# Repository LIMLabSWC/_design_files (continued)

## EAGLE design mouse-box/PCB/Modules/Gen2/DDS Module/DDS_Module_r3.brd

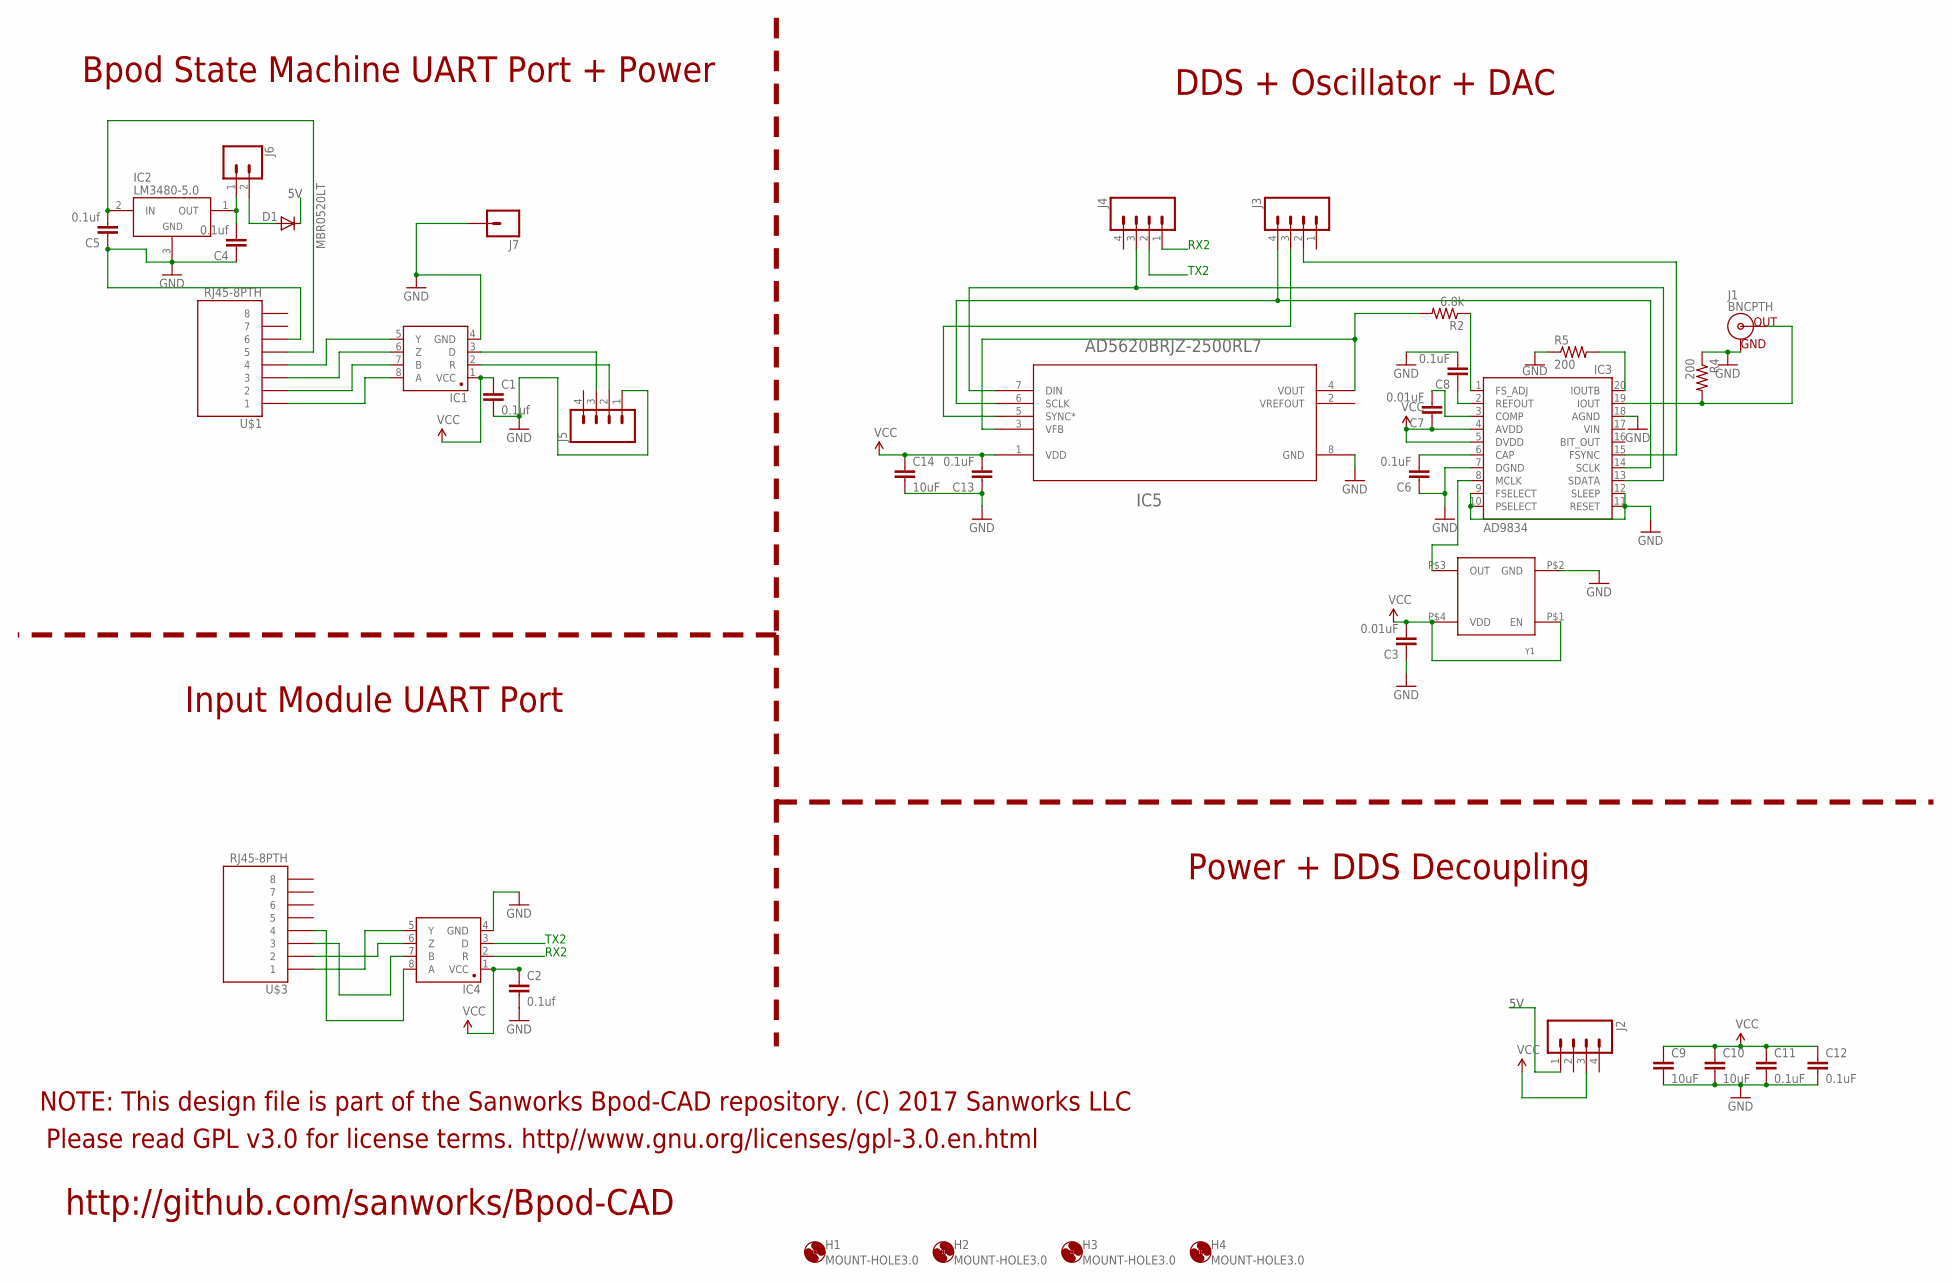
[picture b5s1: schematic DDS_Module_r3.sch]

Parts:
C1, C2, C4, C5: 0.1uf; 1206@1
C3, C7: 0.01uF; 0805
C6, C8, C11, C12, C13: 0.1uF; 0805
C9, C10, C14: 10uF; 0805
D1: MBR0520LT; SOD123
H1, H2, H3, H4: MOUNT-HOLE3.0; 3,0
IC1, IC4: SN65HVD31DR; SO08
IC2: LM3480-5.0; SOT-23-3
IC3: AD9834; TSSOP20
IC5: AD5620BRJZ-2500RL7; RJ_8
J1: BNCPTH; BNC
J2, J3, J4, J5: M04PTH; 1X04
J6: CONN_02; 1X02
J7: M01PTH; 1X01
R2: 6.8k; R0805
R4, R5: 200; R0805
U$1, U$3: RJ45-8PTH; RJ45-8
Y1: ASE10MHZ

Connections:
5V: D1.C, J2.1
GND: C1.2, C2.2, C3.1, C4.1, C5.1, C6.1, C8.2, C9.2, C10.2, C11.2, C12.2, C13.1, C14.2, IC1.4 (GND), IC2.3 (GND), IC3.7 (DGND), IC3.9 (FSELECT), IC3.10 (PSELECT), IC3.11 (RESET), IC3.12 (SLEEP), IC3.18 (AGND), IC4.4 (GND), IC5.8 (GND), J1.GND, J5.1, J7.1, R4.1, R5.1, U$1.6, Y1.P$2 (GND)
unnamed: IC3.13 (SDATA), IC5.7 (DIN), J4.3
unnamed: IC3.14 (SCLK), IC5.6 (SCLK), J3.4
unnamed: IC5.5 (SYNC*), J3.3
unnamed: IC3.20 (IOUTB), R5.2
unnamed: IC3.15 (FSYNC), J3.2
unnamed: IC3.1 (FS_ADJ), R2.1
unnamed: IC1.8 (A), U$1.1
unnamed: IC1.7 (B), U$1.2
unnamed: IC1.6 (Z), U$1.3
unnamed: IC1.5 (Y), U$1.4
unnamed: IC5.3 (VFB), IC5.4 (VOUT), R2.2
unnamed: IC3.8 (MCLK), Y1.P$3 (OUT)
unnamed: IC3.19 (IOUT), J1.S (OUT), R4.2
unnamed: C4.2, IC2.1 (OUT), J6.1
unnamed: C6.2, IC3.6 (CAP)
unnamed: C7.2, IC3.3 (COMP)
unnamed: C8.1, IC3.2 (REFOUT)
unnamed: D1.A, J6.2
unnamed: IC4.5 (Y), U$3.1
unnamed: IC4.6 (Z), U$3.2
unnamed: IC4.7 (B), U$3.3
unnamed: C5.2, IC2.2 (IN), U$1.5
unnamed: IC4.8 (A), U$3.4
RX1: IC1.2 (R), J5.2
RX2: IC4.2 (R), J4.1
TX1: IC1.3 (D), J5.3
TX2: IC4.3 (D), J4.2
VCC: C1.1, C2.1, C3.2, C7.1, C9.1, C10.1, C11.1, C12.1, C13.2, C14.1, IC1.1 (VCC), IC3.4 (AVDD), IC3.5 (DVDD), IC4.1 (VCC), IC5.1 (VDD), J2.3, Y1.P$1 (EN), Y1.P$4 (VDD)

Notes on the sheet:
RX2
TX2
Bpod State Machine UART Port + Power
Input Module UART Port
DDS + Oscillator + DAC
Power + DDS Decoupling
Please read GPL v3.0 for license terms. http//www.gnu.org/licenses/gpl-3.0.en.html
NOTE: This design file is part of the Sanworks Bpod-CAD repository. (C) 2017 Sanworks LLC
http://github.com/sanworks/Bpod-CAD

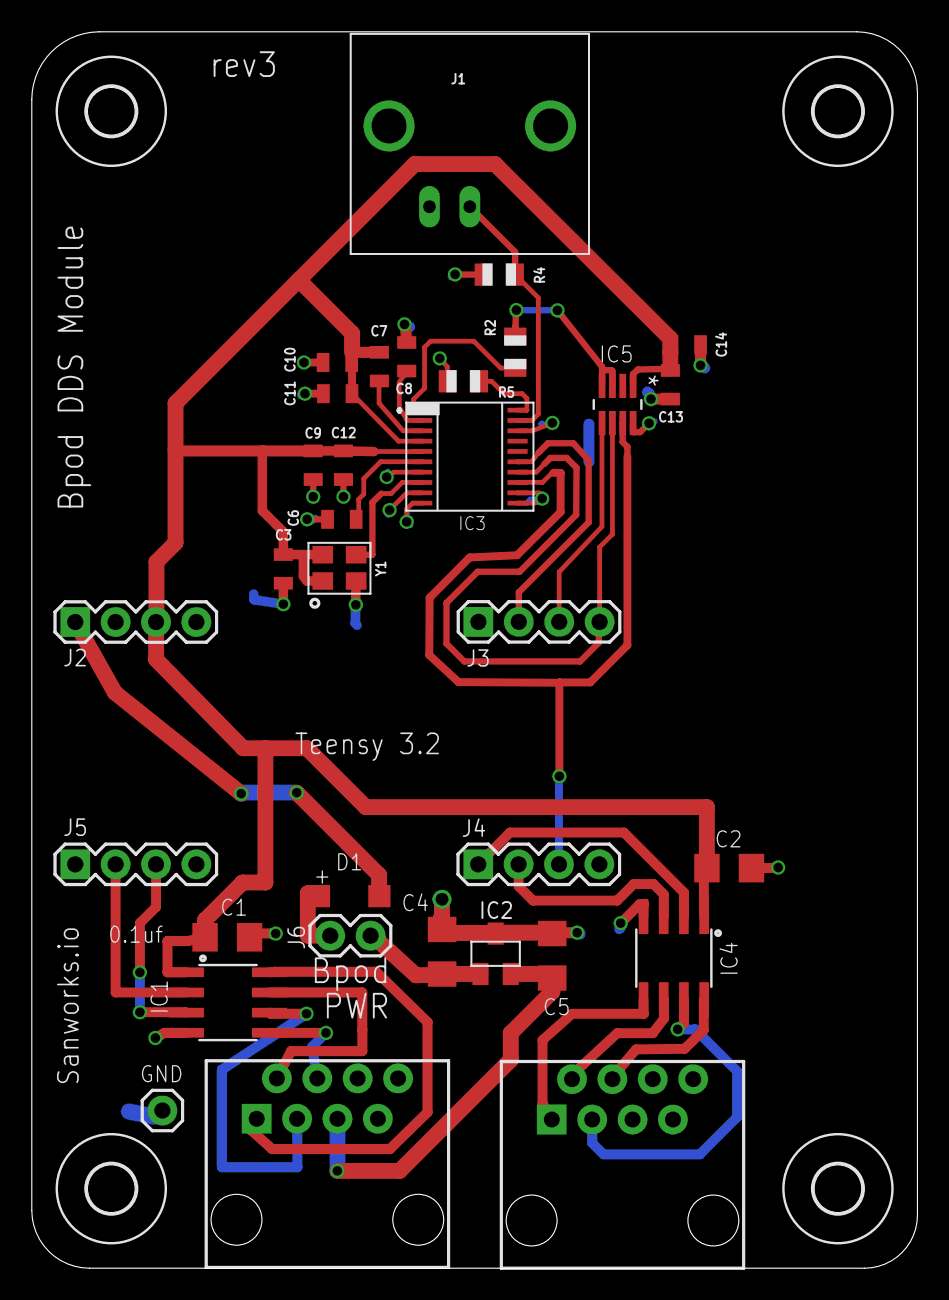
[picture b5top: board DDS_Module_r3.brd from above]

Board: 2 copper layers, 55.7 x 77.8 mm, 37 parts (0 on the bottom side), 30 nets.

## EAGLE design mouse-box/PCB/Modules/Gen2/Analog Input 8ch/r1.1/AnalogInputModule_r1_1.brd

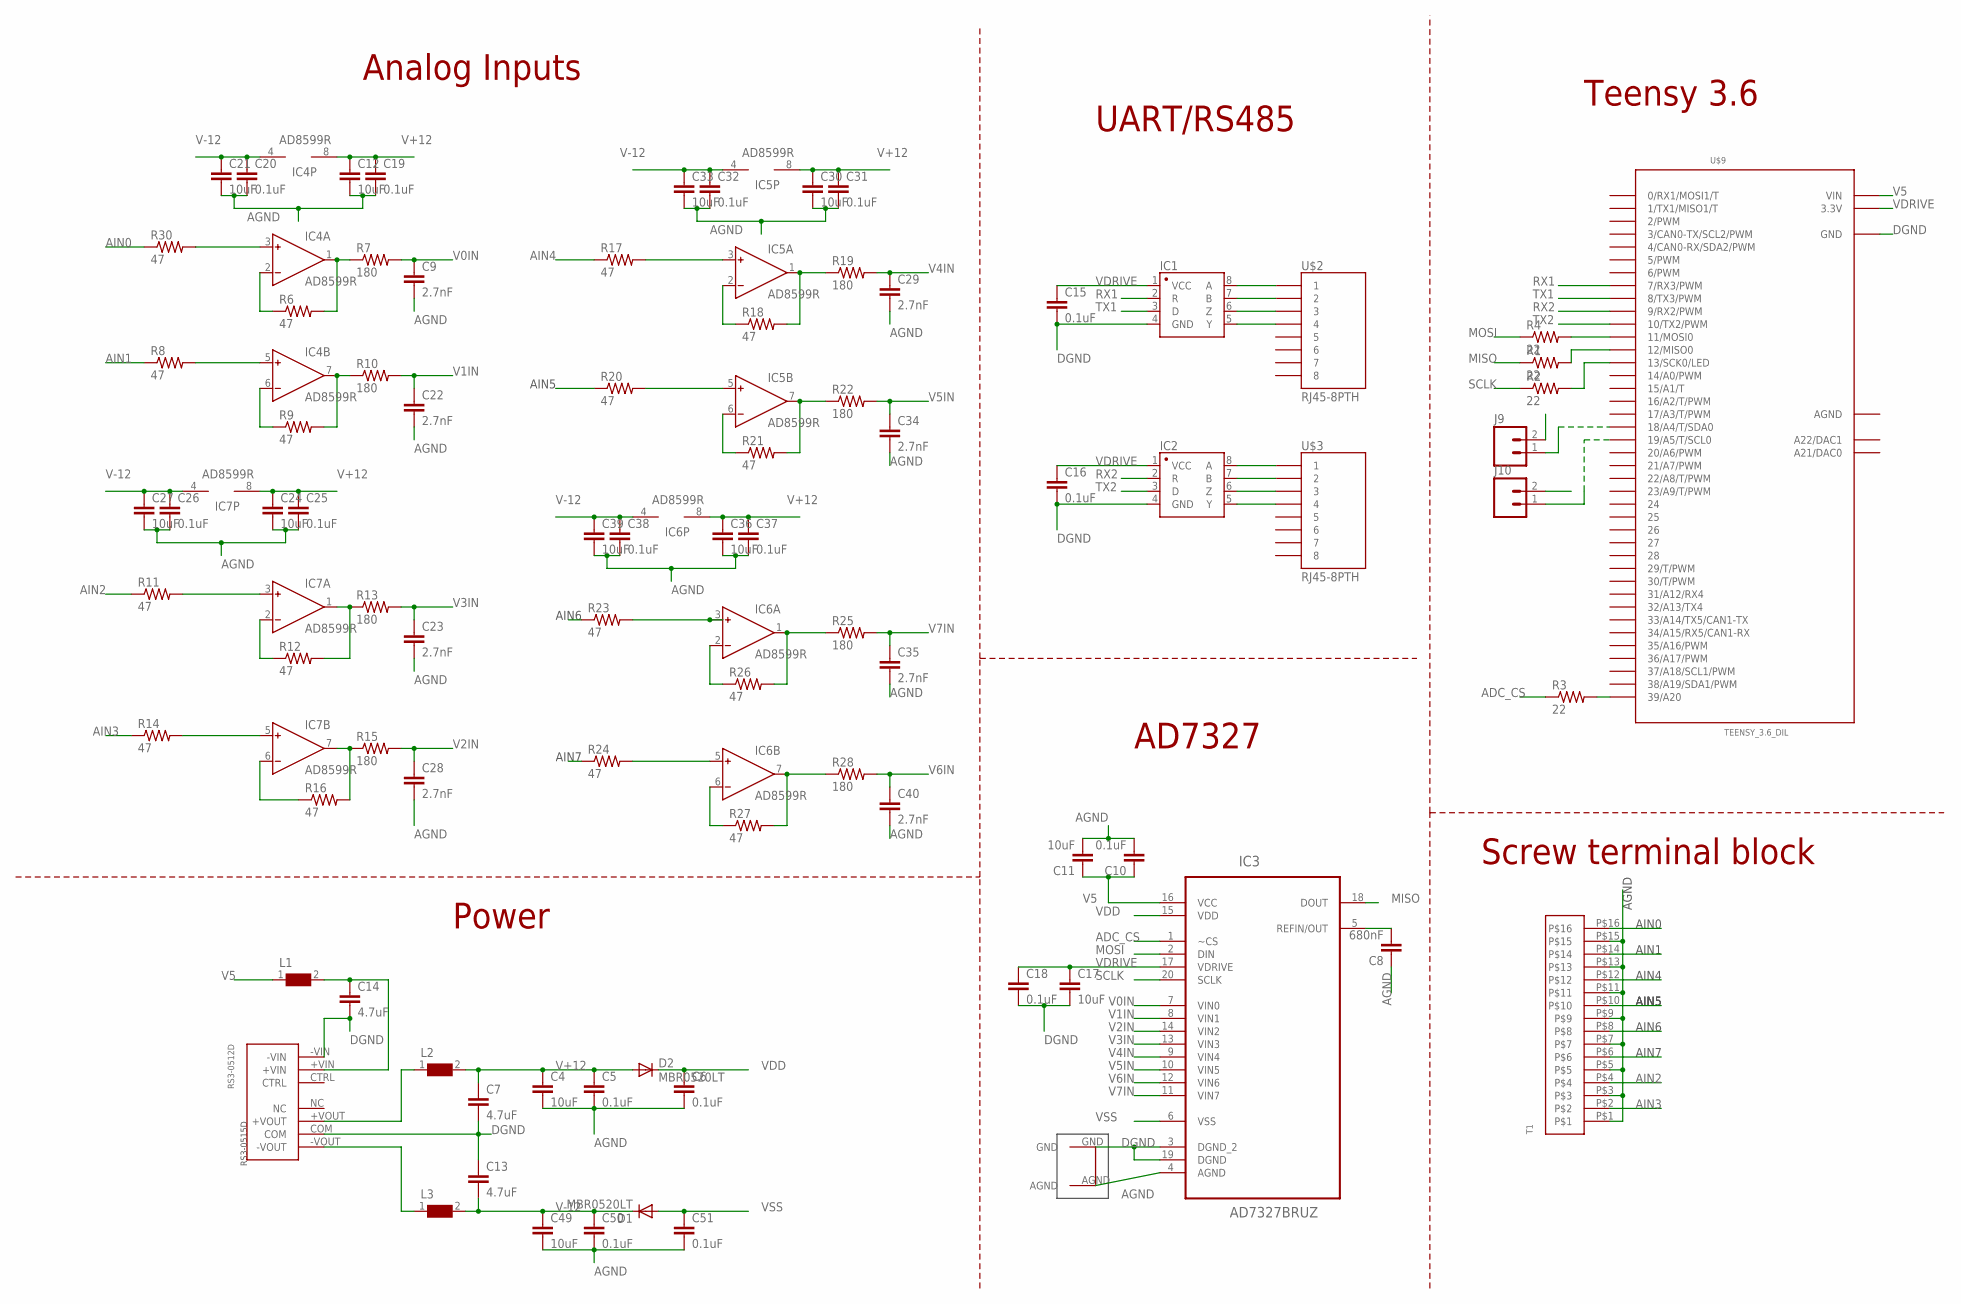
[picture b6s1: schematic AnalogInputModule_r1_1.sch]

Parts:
C4, C11, C12, C17, C21, C24, C27, C30, C33, C36, C39, C49: 10uF; 0805
C5, C6, C10, C15, C16, C18, C19, C20, C25, C26, C31, C32, C37, C38, C50, C51: 0.1uF; 0805
C7, C13, C14: 4.7uF; 1206
C8: 680nF; 0805
C9, C22, C23, C28, C29, C34, C35, C40: 2.7nF; 0805
D1, D2: MBR0520LT; SOD123
IC1, IC2: SN65HVD31DR; SO08
IC3: AD7327BRUZ; SOP65P640X120-20N
IC4, IC5, IC6, IC7: AD8599R; SO8
J9, J10: M023.5MM; SCREWTERMINAL-3.5MM-2
L1, L2, L3: WE-CBF-742792118_1206; 1206
R1, R2, R3, R4: 22; R0805
R6, R8, R9, R11, R12, R14, R16, R17, R18, R20, R21, R23, R24, R26, R27, R30: 47; R0805
R7, R10, R13, R15, R19, R22, R25, R28: 180; R0805
RS3-0512D: RS3-0515D
T1: 16POS_SCREWTERMINAL
U$2, U$3: RJ45-8PTH; RJ45-8
U$4: GNDPLANESHRT
U$9: TEENSY_3.6_DIL

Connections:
+VOUT: L2.1, RS3-0512D.+VOUT
-VOUT: L3.1, RS3-0512D.-VOUT
ADC_CS: IC3.1 (~CS), R3.1
AGND: C4.2, C5.2, C6.2, C8.1, C9.2, C10.2, C11.2, C12.2, C19.2, C20.2, C21.2, C22.2, C23.2, C24.2, C25.2, C26.2, C27.2, C28.2, C29.2, C30.2, C31.2, C32.2, C33.2, C34.2, C35.2, C36.2, C37.2, C38.2, C39.2, C40.2, C49.2, C50.2, C51.2, IC3.4 (AGND), T1.P$1, T1.P$3, T1.P$5, T1.P$7, T1.P$9, T1.P$11, T1.P$13, T1.P$15, U$4.AGND, U$9.AGND
AIN0: R30.1, T1.P$16
AIN1: R8.1, T1.P$14
AIN2: R11.1, T1.P$4
AIN3: R14.1, T1.P$2
AIN4: R17.1, T1.P$12
AIN5: R20.1, T1.P$10
AIN6: R23.1, T1.P$8
AIN7: R24.1, T1.P$6
DGND: C7.2, C13.1, C14.2, C15.2, C16.2, C17.2, C18.2, IC1.4 (GND), IC2.4 (GND), IC3.3 (DGND_2), IC3.19 (DGND), J9.2, J10.2, RS3-0512D.-VIN, RS3-0512D.COM, U$4.GND, U$9.GND, U$9.GND1 (GND)
MISO: IC3.18 (DOUT), R1.1
MOSI: IC3.2 (DIN), R4.1
unnamed: IC1.6 (Z), U$2.3
unnamed: IC1.8 (A), U$2.1
unnamed: IC1.5 (Y), U$2.4
unnamed: IC1.7 (B), U$2.2
unnamed: IC2.6 (Z), U$3.3
unnamed: IC2.5 (Y), U$3.4
unnamed: IC2.8 (A), U$3.1
unnamed: IC2.7 (B), U$3.2
unnamed: R4.2, U$9.11 (11/MOSI0)
unnamed: R1.2, U$9.12 (12/MISO0)
unnamed: C14.1, L1.2, RS3-0512D.+VIN
unnamed: R3.2, U$9.39/A20
unnamed: IC4.3 (IN+), R30.2
unnamed: R2.2, U$9.13 (13/SCK0/LED)
unnamed: IC4.2 (IN-), R6.1
unnamed: IC4.1 (OUT), R6.2, R7.1
unnamed: J9.1, U$9.18/A4 (18/A4/T/SDA0)
unnamed: J10.1, U$9.19/A5 (19/A5/T/SCL0)
unnamed: IC4.5 (IN+), R8.2
unnamed: IC4.6 (IN-), R9.1
unnamed: IC4.7 (OUT), R9.2, R10.1
unnamed: IC7.3 (IN+), R11.2
unnamed: IC7.2 (IN-), R12.1
unnamed: IC7.1 (OUT), R12.2, R13.1
unnamed: IC7.5 (IN+), R14.2
unnamed: IC7.6 (IN-), R16.1
unnamed: IC7.7 (OUT), R15.1, R16.2
unnamed: IC5.3 (IN+), R17.2
unnamed: IC5.2 (IN-), R18.1
unnamed: IC5.1 (OUT), R18.2, R19.1
unnamed: IC5.5 (IN+), R20.2
unnamed: IC5.6 (IN-), R21.1
unnamed: IC5.7 (OUT), R21.2, R22.1
unnamed: IC6.3 (IN+), R23.2
unnamed: IC6.2 (IN-), R26.1
unnamed: IC6.1 (OUT), R25.1, R26.2
unnamed: IC6.5 (IN+), R24.2
unnamed: IC6.6 (IN-), R27.1
unnamed: IC6.7 (OUT), R27.2, R28.1
REF: C8.2, IC3.5 (REFIN/OUT)
RX1: IC1.2 (R), U$9.7 (7/RX3/PWM)
RX2: IC2.2 (R), U$9.9 (9/RX2/PWM)
SCLK: IC3.20 (SCLK), R2.1
TX1: IC1.3 (D), U$9.8 (8/TX3/PWM)
TX2: IC2.3 (D), U$9.10 (10/TX2/PWM)
V0IN: C9.1, IC3.7 (VIN0), R7.2
V1IN: C22.1, IC3.8 (VIN1), R10.2
V2IN: C28.1, IC3.14 (VIN2), R15.2
V3IN: C23.1, IC3.13 (VIN3), R13.2
V4IN: C29.1, IC3.9 (VIN4), R19.2
V5: C10.1, C11.1, IC3.16 (VCC), L1.1, U$9.VIN
V5IN: C34.1, IC3.10 (VIN5), R22.2
V6IN: C40.1, IC3.12 (VIN6), R28.2
V7IN: C35.1, IC3.11 (VIN7), R25.2
V+12: C4.1, C5.1, C7.1, C12.1, C19.1, C24.1, C25.1, C30.1, C31.1, C36.1, C37.1, D2.A, IC4.8 (V+), IC5.8 (V+), IC6.8 (V+), IC7.8 (V+), L2.2
V-12: C13.2, C20.1, C21.1, C26.1, C27.1, C32.1, C33.1, C38.1, C39.1, C49.1, C50.1, D1.C, IC4.4 (V-), IC5.4 (V-), IC6.4 (V-), IC7.4 (V-), L3.2
VDD: C6.1, D2.C, IC3.15 (VDD)
VDRIVE: C15.1, C16.1, C17.1, C18.1, IC1.1 (VCC), IC2.1 (VCC), IC3.17 (VDRIVE), U$9.3.3V, U$9.3.3V3 (3.3V)
VSS: C51.1, D1.A, IC3.6 (VSS)

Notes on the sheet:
Teensy 3.6
UART/RS485
AD7327
Analog Inputs
Power
Screw terminal block
AIN7
AIN6
AIN5
AIN4
AIN1
AIN0
AGND

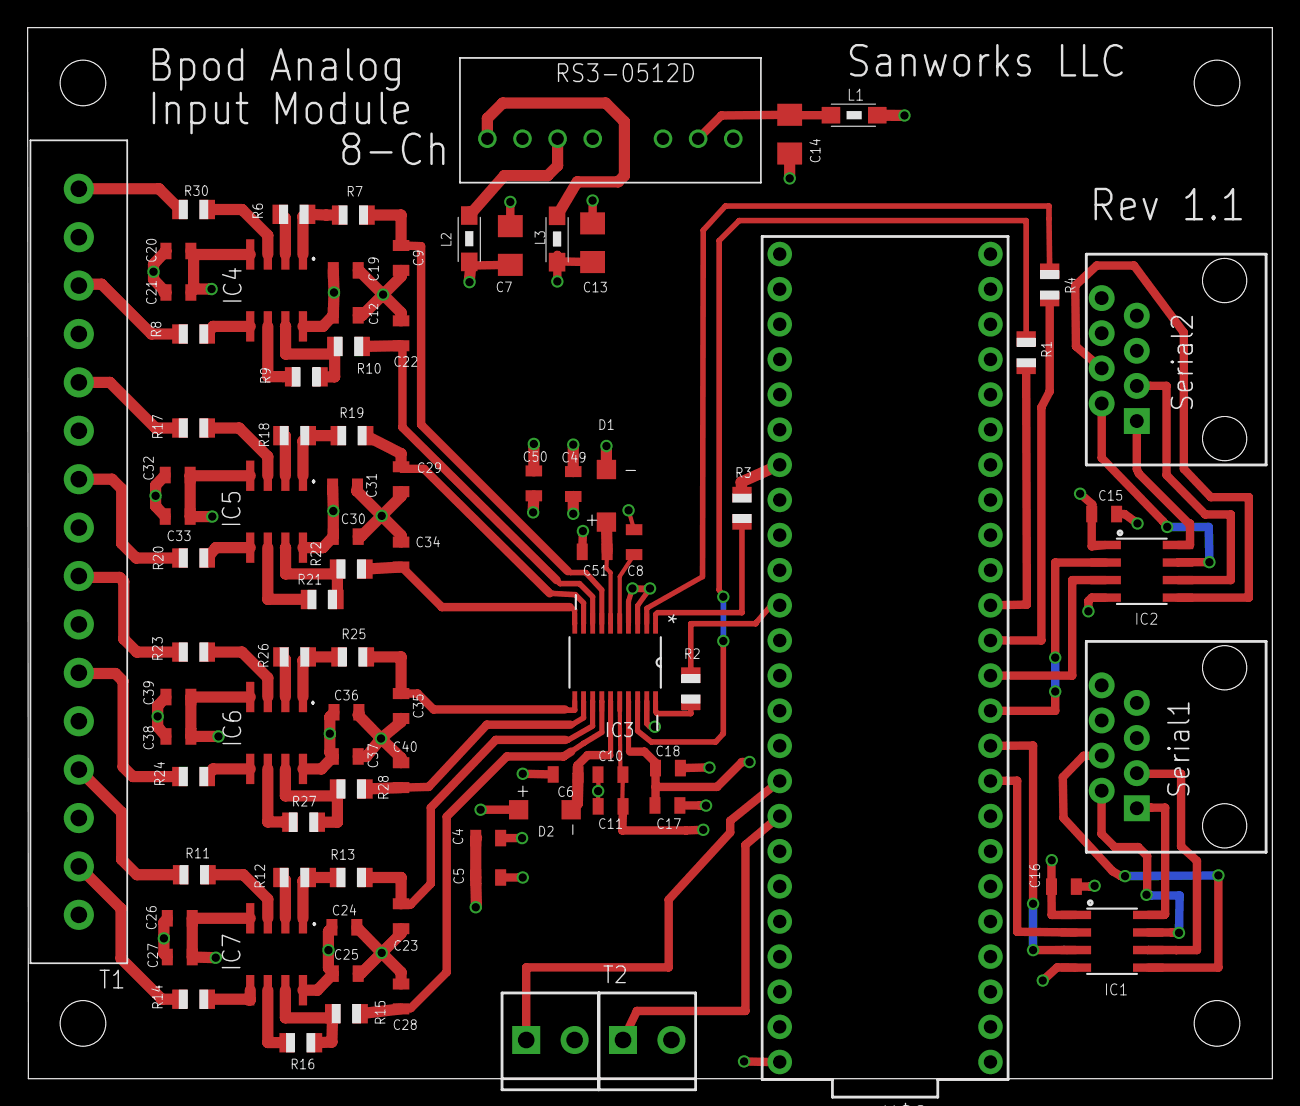
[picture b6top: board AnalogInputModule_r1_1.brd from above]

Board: 4 copper layers, 90.0 x 76.0 mm, 92 parts (0 on the bottom side), 74 nets.

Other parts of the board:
U$5, U$6, U$7, U$8: STAND-OFF

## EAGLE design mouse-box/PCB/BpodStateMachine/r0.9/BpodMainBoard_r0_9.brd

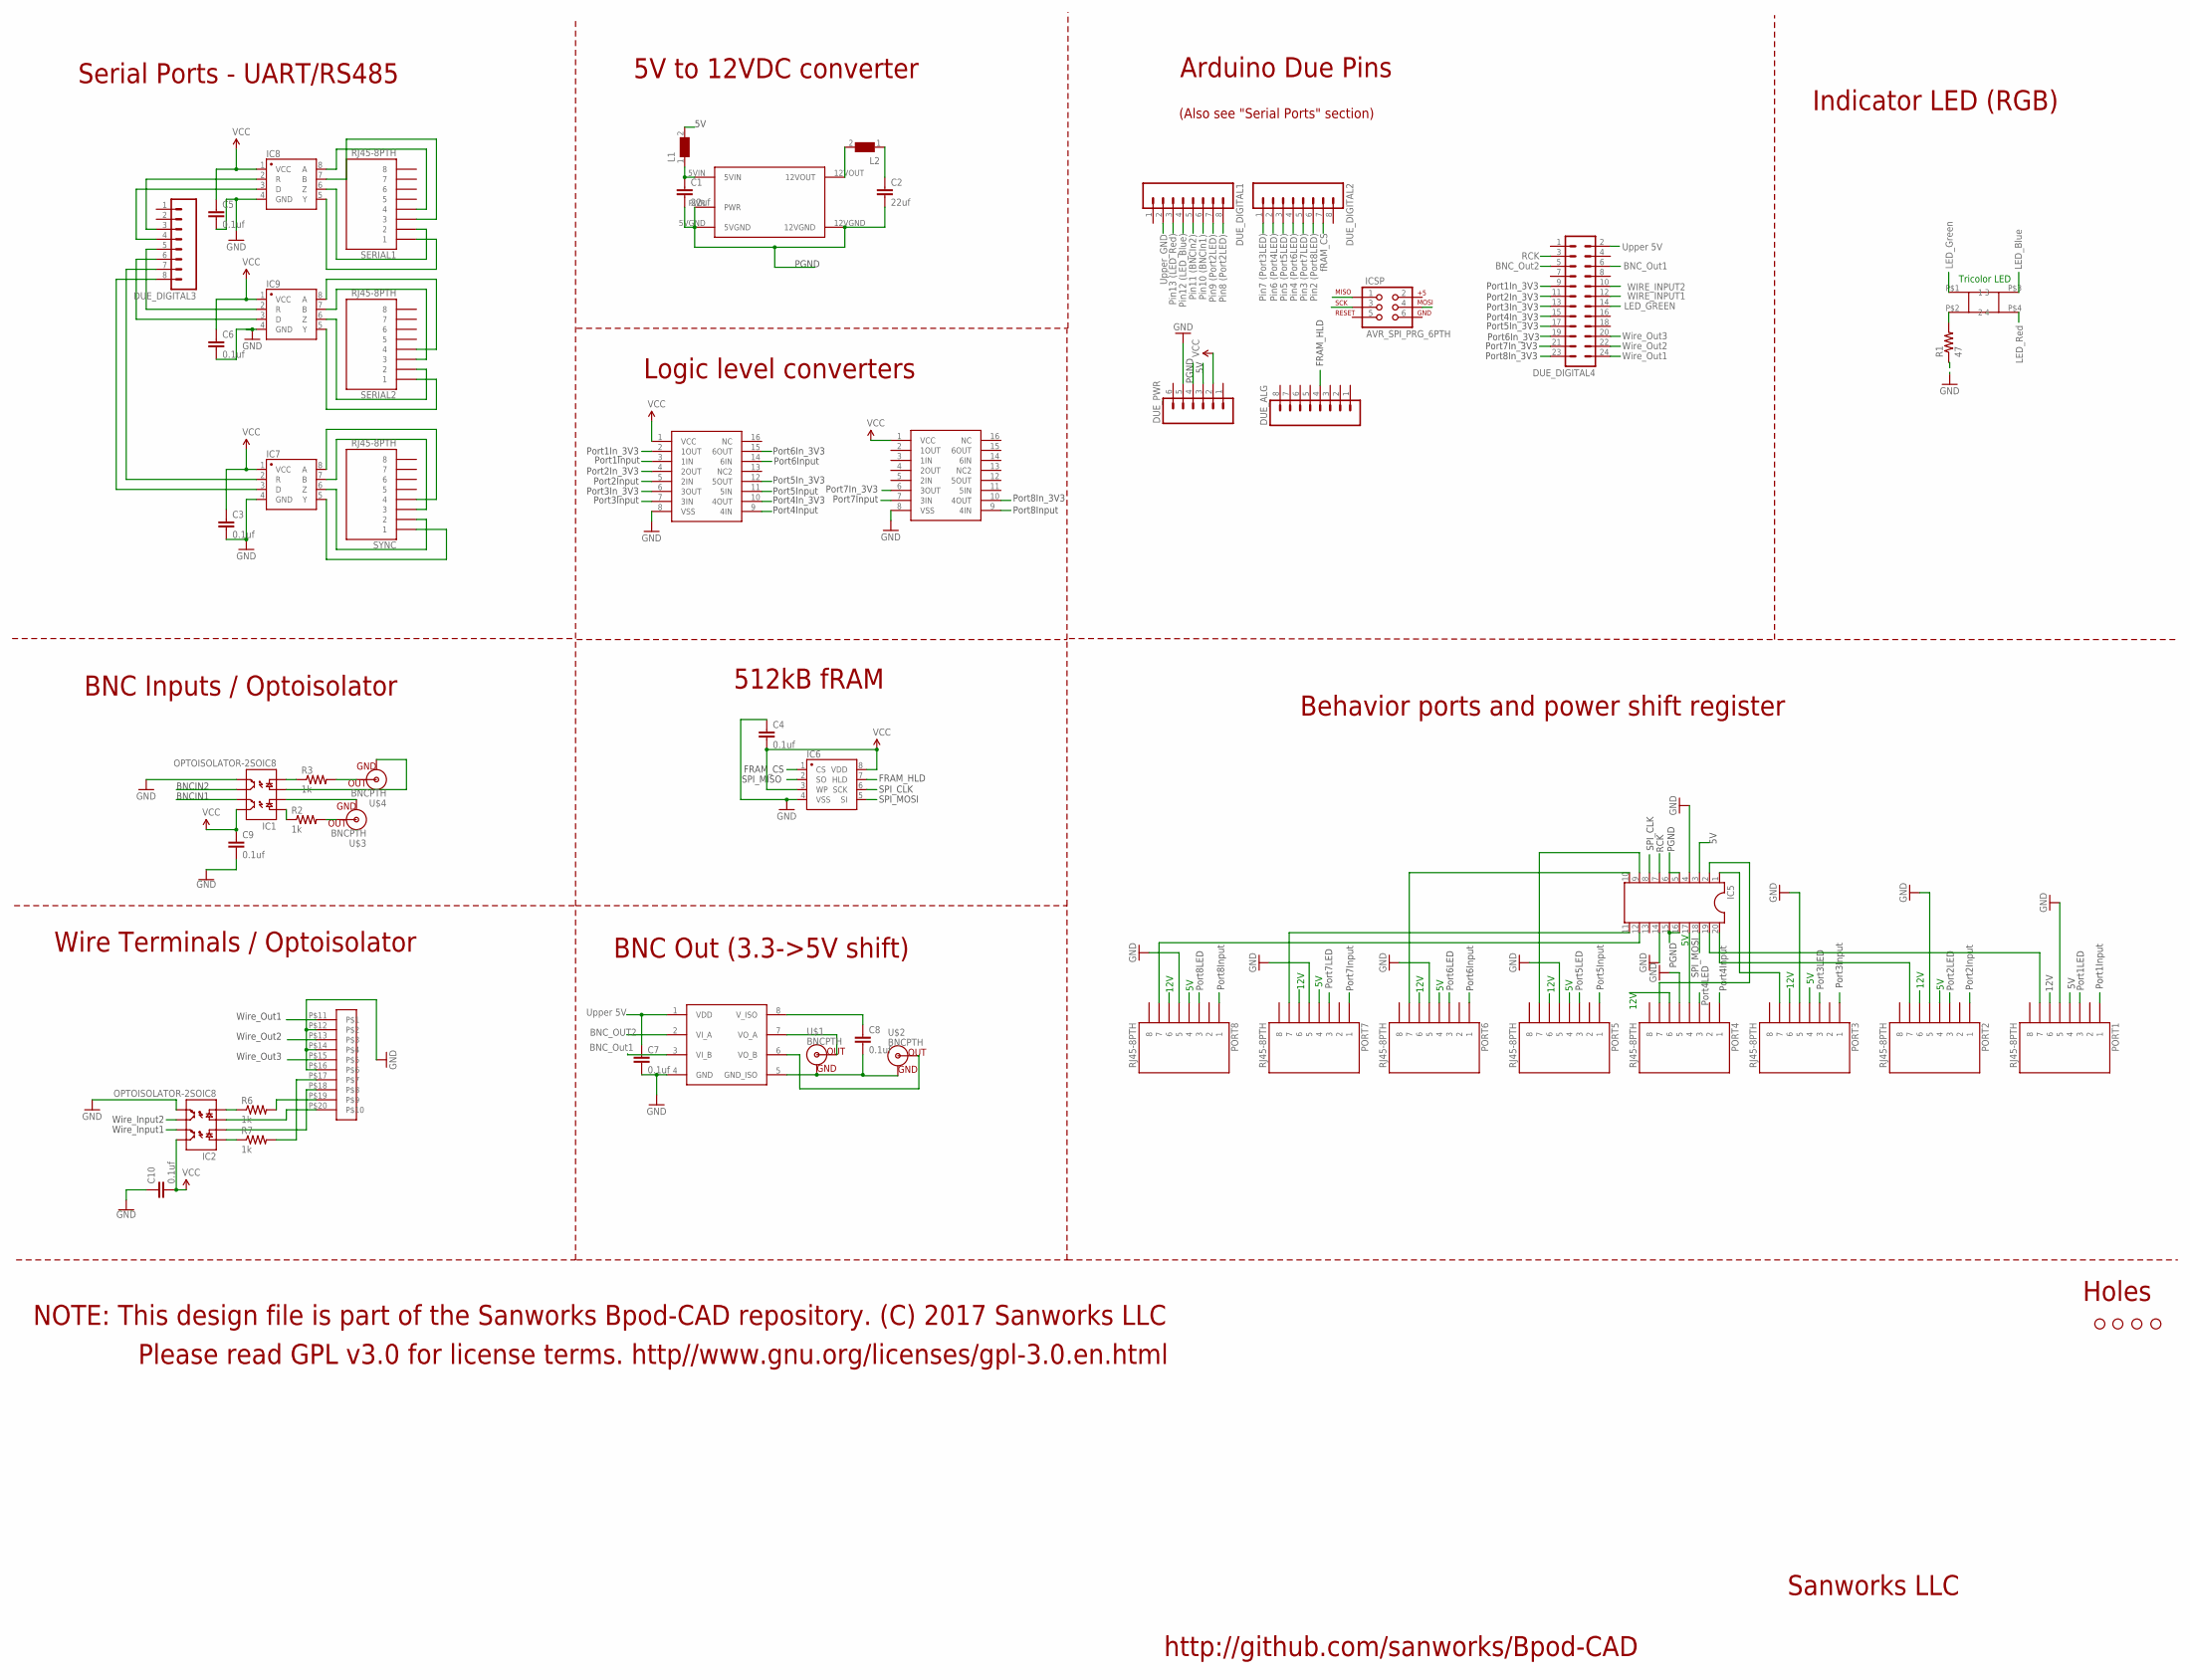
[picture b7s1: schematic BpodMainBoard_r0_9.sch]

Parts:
C1, C2: 22uf; 1206
C3, C4, C5, C6, C7, C8, C9, C10: 0.1uf; 1206
DUE_ALG: M081X08; 1X08
DUE_DIGITAL1, DUE_DIGITAL2, DUE_DIGITAL3: M081X08; 1X08
DUE_DIGITAL4: MA12-2
DUE_PWR: M06SIP; 1X06
IC1, IC2: OPTOISOLATOR-2SOIC8; SO08-2
IC3, IC4: CD4050; SO16
IC5: DIL20
IC6: CY15B104Q-SXI; SO08-UNIVERSAL
IC7, IC8, IC9: SN65HVD31DR; SO08
IC10: ADUM5240; SO08
ICSP: AVR_SPI_PRG_6PTH; 2X3
JP1, JP2, JP3, JP4: STAND-OFF
L1: WE-CBF-742792118_1206; 1206
L2: WE-CBF-742792118_1206; 1206; MPN 742792118
PORT1, PORT2, PORT3, PORT4, PORT5, PORT6, PORT7, PORT8: RJ45-8PTH; RJ45-8
R1: 47; 1206
R2, R3, R6, R7: 1k; 1206
SERIAL1, SERIAL2: RJ45-8PTH; RJ45-8
SYNC: RJ45-8PTH; RJ45-8
U$1, U$2, U$3, U$4: BNCPTH; BNC
U$5: TDK_LAMBDA_5V_TO_12V; TDK_LAMBDA_5V_12V
U$6: 10POS_SPRING_TERMINAL; 10POS_SCREW_TERMINAL
U$8: SQUARE_TRICOLOR_LED

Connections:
5V: DUE_PWR.3, IC5.3, IC5.17, L1.2, PORT1.4, PORT2.4, PORT3.4, PORT4.4, PORT5.4, PORT6.4, PORT7.4, PORT8.4
12V: C2.1, L2.1, PORT1.6, PORT2.6, PORT3.6, PORT4.6, PORT5.6, PORT6.6, PORT7.6, PORT8.6
BNCIN1: DUE_DIGITAL1.6, IC1.7 (EM1)
BNCIN2: DUE_DIGITAL1.5, IC1.6 (CL2)
BNC_OUT1: DUE_DIGITAL4.6, IC10.3 (VI_B)
BNC_OUT2: DUE_DIGITAL4.5, IC10.2 (VI_A)
FRAM_CS: DUE_DIGITAL2.7, IC6.1 (CS)
FRAM_HLD: DUE_ALG.4, IC6.7 (HLD)
GND: C3.2, C5.2, C6.2, C7.2, C9.2, C10.1, DUE_PWR.5, IC1.5 (EM2), IC2.5 (EM2), IC3.8 (VSS), IC4.8 (VSS), IC5.4, IC5.14, IC6.4 (VSS), IC7.4 (GND), IC8.4 (GND), IC9.4 (GND), IC10.4 (GND), PORT1.5, PORT2.5, PORT3.5, PORT4.5, PORT5.5, PORT6.5, PORT7.5, PORT8.5, R1.1, U$6.P$12, U$6.P$14, U$6.P$16
ISOGND: C8.2, IC10.5 (GND_ISO), U$1.GND, U$2.GND
LED_BLUE: DUE_DIGITAL1.4, U$8.P$3 (3)
LED_GREEN: DUE_DIGITAL4.14, U$8.P$1 (1)
LED_RED: DUE_DIGITAL1.3, U$8.P$4 (4)
MOSI: IC5.18, IC6.5 (SI), ICSP.4
unnamed: R3.2, U$4.S (OUT)
unnamed: R2.2, U$3.S (OUT)
unnamed: IC1.3 (A2), U$4.GND
unnamed: IC1.2 (C1), U$3.GND
unnamed: R6.2, U$6.P$19
unnamed: IC10.6 (VO_B), U$2.S (OUT)
unnamed: IC10.7 (VO_A), U$1.S (OUT)
unnamed: IC5.19, PORT1.7
unnamed: IC5.20, PORT2.7
unnamed: IC5.1, PORT3.7
unnamed: IC5.2, PORT4.7
unnamed: IC5.9, PORT5.7
unnamed: IC5.10, PORT6.7
unnamed: IC5.11, PORT7.7
unnamed: IC5.12, PORT8.7
unnamed: IC7.8 (A), SYNC.4
unnamed: IC7.7 (B), SYNC.3
unnamed: IC7.6 (Z), SYNC.2
unnamed: IC7.5 (Y), SYNC.1
unnamed: DUE_DIGITAL3.7, IC7.2 (R)
unnamed: IC2.4 (C2), R6.1
unnamed: IC2.1 (A1), R7.1
unnamed: R1.2, U$8.P$2 (2)
unnamed: C8.1, IC10.8 (V_ISO)
unnamed: DUE_DIGITAL3.8, IC7.3 (D)
unnamed: IC8.8 (A), SERIAL1.4
unnamed: IC8.7 (B), SERIAL1.3
unnamed: IC8.6 (Z), SERIAL1.2
unnamed: IC8.5 (Y), SERIAL1.1
unnamed: IC9.8 (A), SERIAL2.4
unnamed: IC9.7 (B), SERIAL2.3
unnamed: IC9.6 (Z), SERIAL2.2
unnamed: IC9.5 (Y), SERIAL2.1
unnamed: DUE_DIGITAL3.3, IC8.2 (R)
unnamed: IC2.3 (A2), U$6.P$20
unnamed: R7.2, U$6.P$17
unnamed: IC2.2 (C1), U$6.P$18
unnamed: C1.1, L1.1, U$5.5VIN
unnamed: L2.2, U$5.12VOUT
unnamed: DUE_DIGITAL3.4, IC8.3 (D)
unnamed: DUE_DIGITAL3.5, IC9.2 (R)
unnamed: DUE_DIGITAL3.6, IC9.3 (D)
unnamed: IC1.1 (A1), R2.1
unnamed: IC1.4 (C2), R3.1
PGND: C1.2, C2.2, DUE_PWR.4, IC5.5, IC5.6, IC5.15, IC5.16, U$5.5VGND, U$5.12VGND, U$5.PWR
PORT1INPUT: IC3.3 (1IN), PORT1.1
PORT1IN_3V3: DUE_DIGITAL4.9, IC3.2 (1OUT)
PORT1LED: DUE_DIGITAL1.7, PORT1.3
PORT2INPUT: IC3.5 (2IN), PORT2.1
PORT2IN_3V3: DUE_DIGITAL4.11, IC3.4 (2OUT)
PORT2LED: DUE_DIGITAL1.8, PORT2.3
PORT3INPUT: IC3.7 (3IN), PORT3.1
PORT3IN_3V3: DUE_DIGITAL4.13, IC3.6 (3OUT)
PORT3LED: DUE_DIGITAL2.1, PORT3.3
PORT4INPUT: IC3.9 (4IN), PORT4.1
PORT4IN_3V3: DUE_DIGITAL4.15, IC3.10 (4OUT)
PORT4LED: DUE_DIGITAL2.2, PORT4.3
PORT5INPUT: IC3.11 (5IN), PORT5.1
PORT5IN_3V3: DUE_DIGITAL4.17, IC3.12 (5OUT)
PORT5LED: DUE_DIGITAL2.3, PORT5.3
PORT6INPUT: IC3.14 (6IN), PORT6.1
PORT6IN_3V3: DUE_DIGITAL4.19, IC3.15 (6OUT)
PORT6LED: DUE_DIGITAL2.4, PORT6.3
PORT7INPUT: IC4.7 (3IN), PORT7.1
PORT7IN_3V3: DUE_DIGITAL4.21, IC4.6 (3OUT)
PORT7LED: DUE_DIGITAL2.5, PORT7.3
PORT8INPUT: IC4.9 (4IN), PORT8.1
PORT8IN_3V3: DUE_DIGITAL4.23, IC4.10 (4OUT)
PORT8LED: DUE_DIGITAL2.6, PORT8.3
RCK: DUE_DIGITAL4.3, IC5.7
SPI_CLK: IC5.8, IC6.6 (SCK), ICSP.3
SPI_MISO: IC6.2 (SO), ICSP.1
UPPER_5V: C7.1, DUE_DIGITAL4.2, IC10.1 (VDD)
UPPER_GND: DUE_DIGITAL1.2
VCC: C3.1, C4.2, C5.1, C6.1, C9.1, C10.2, DUE_PWR.2, IC1.8 (CL1), IC2.8 (CL1), IC3.1 (VCC), IC4.1 (VCC), IC6.3 (WP), IC6.8 (VDD), IC7.1 (VCC), IC8.1 (VCC), IC9.1 (VCC)
WIREOUT3: DUE_DIGITAL4.20, U$6.P$15
WIRE_INPUT1: DUE_DIGITAL4.12, IC2.7 (EM1)
WIRE_INPUT2: DUE_DIGITAL4.10, IC2.6 (CL2)
WIRE_OUT1: DUE_DIGITAL4.24, U$6.P$11
WIRE_OUT2: DUE_DIGITAL4.22, U$6.P$13

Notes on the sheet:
12V
Pin10 (BNCIn1)
Pin11 (BNCIn2)
Tricolor LED
BNCIN1
BNCIN2
PGND
Upper 5V
Pin12 (LED_Blue)
Pin13 (LED_Red)
Upper_GND
Pin8 (Port2LED)
Pin9 (Port2LED)
Pin7 (Port3LED)
Pin6 (Port4LED)
Pin5 (Port5LED)
Pin4 (Port6LED)
Pin3 (Port7LED)
Pin2 (Port8LED)
fRAM_CS
Port1LED
Serial Ports - UART/RS485
BNC Inputs / Optoisolator
Port2LED
5V to 12VDC converter
Sanworks LLC
Port3LED
Port4LED
Port5LED
Port6LED
Port7LED
Port8LED
Logic level converters
Port1Input
Port2Input
Port3Input
Port4Input
Port5Input
Port6Input
Port7Input

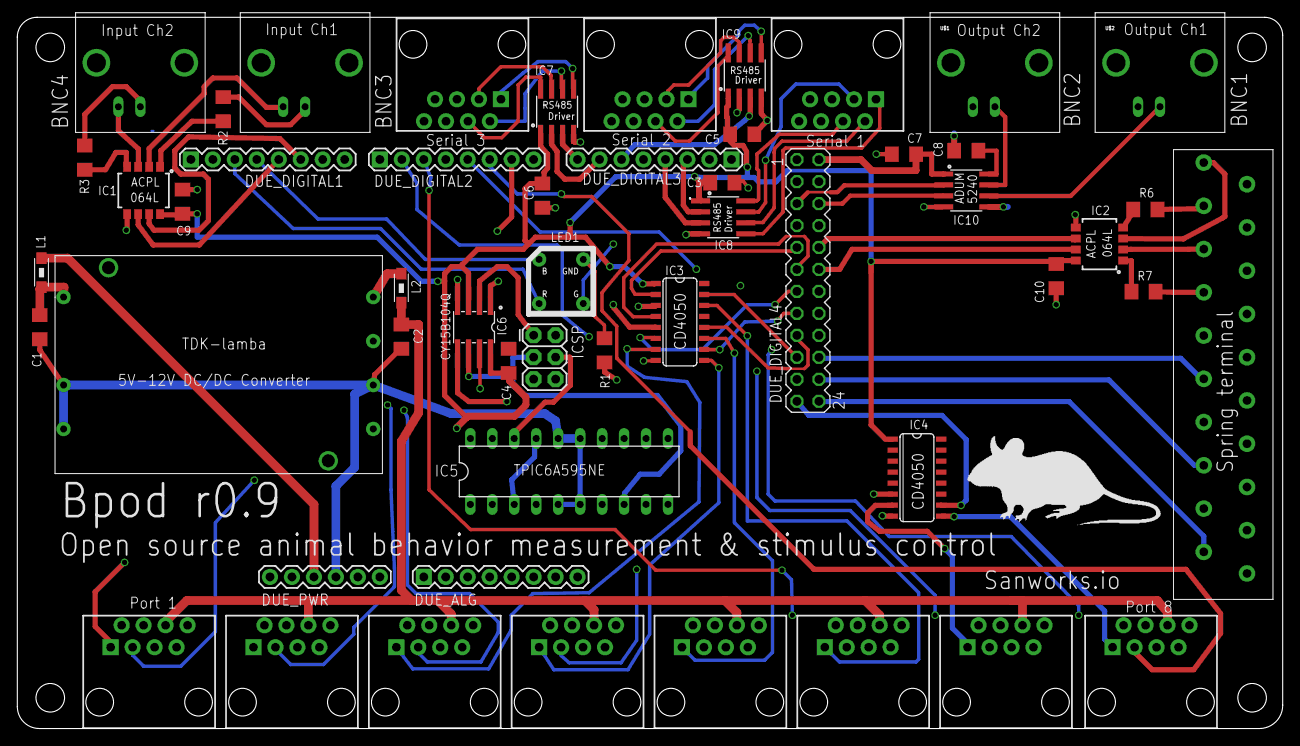
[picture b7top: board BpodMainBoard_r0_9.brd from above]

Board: 4 copper layers, 146.3 x 82.2 mm, 57 parts (0 on the bottom side), 93 nets.

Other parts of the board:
U$7: MOUSELOGO

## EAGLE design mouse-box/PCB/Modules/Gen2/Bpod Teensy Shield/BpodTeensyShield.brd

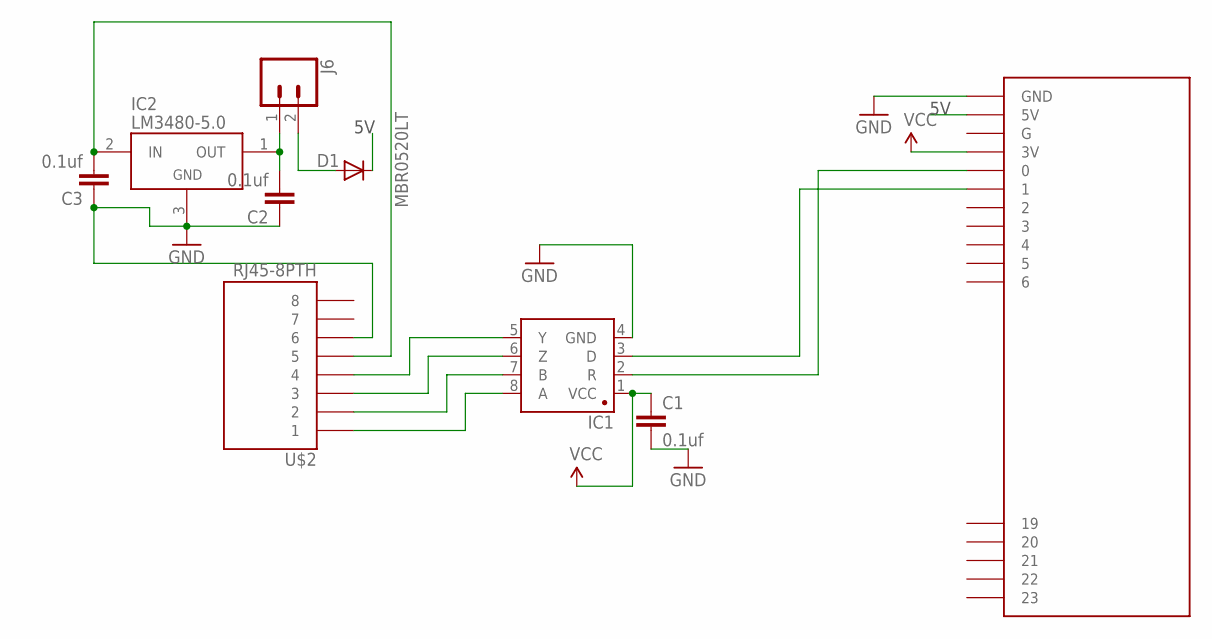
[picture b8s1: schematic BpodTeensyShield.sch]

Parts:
C1, C2, C3: 0.1uf; 1206@1
D1: MBR0520LT; SOD123
IC1: SN65HVD31DR; SO08
IC2: LM3480-5.0; SOT-23-3
J6: CONN_02; 1X02
U$1: AUDIOSHIELD
U$2: RJ45-8PTH; RJ45-8

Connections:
5V: D1.C, U$1.5V
GND: C1.2, C2.1, C3.1, IC1.4 (GND), IC2.3 (GND), U$1.GND, U$2.6
unnamed: IC1.8 (A), U$2.1
unnamed: IC1.7 (B), U$2.2
unnamed: IC1.6 (Z), U$2.3
unnamed: IC1.5 (Y), U$2.4
unnamed: C2.2, IC2.1 (OUT), J6.1
unnamed: D1.A, J6.2
unnamed: C3.2, IC2.2 (IN), U$2.5
RX1: IC1.2 (R), U$1.0
TX1: IC1.3 (D), U$1.1
VCC: C1.1, IC1.1 (VCC), U$1.3V

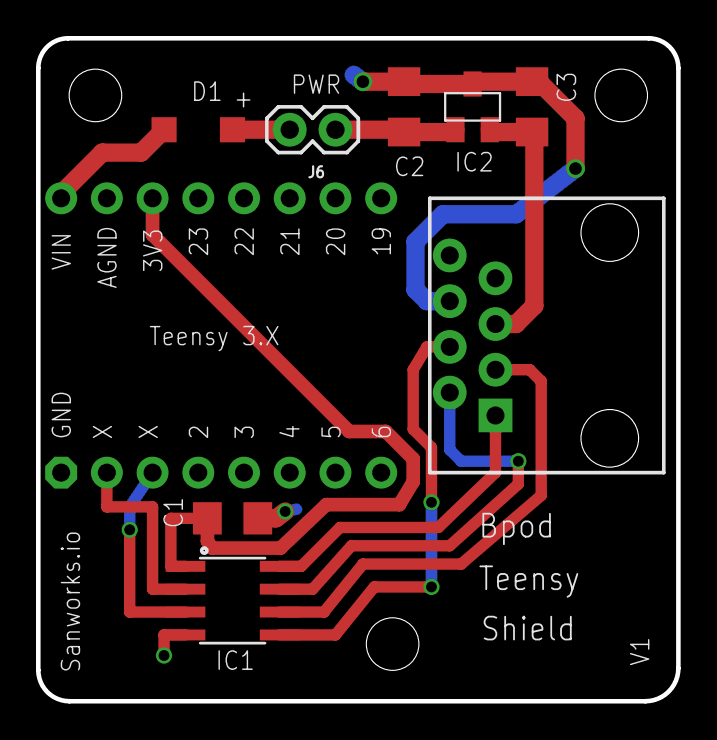
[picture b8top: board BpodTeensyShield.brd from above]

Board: 2 copper layers, 35.6 x 36.8 mm, 9 parts (0 on the bottom side), 12 nets.

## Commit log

2025-02-04 adding rig files
2025-02-04 adding mouse box
2025-05-06 Add Edmunds_designs submodule for Edmund's Inventro repo
2025-06-25 add gitignore file
2025-06-25 add neuropixels config files
2025-07-01 add np implant designs
2025-07-01 remover .DS_Store, update gitignore
2025-07-01 add quick start section to README.md
2025-07-01 add folder specific readme files
2025-07-01 rename files and folders to follow naming convention
2025-07-01 add old version README fies
2025-07-01 Update Edmunds_designs submodule after cleanup
2025-07-01 remove Thumbs.db, add to gitignore
2025-07-01 Reset Edmunds_designs submodule to remote state
2025-07-01 Update Edmunds_designs submodule to latest commit
2025-07-01 Track post-merge submodule sync hook
2025-07-01 add setup script
2025-07-01 remove junk
2025-07-01 add design files for tall rig
2025-07-01 update rat rig readme
2025-07-01 remove junk, update gitignore
2025-07-02 update Edmund's designs
2025-07-02 add nose port PCB assembly figure
2025-07-11 add modified ceiling shelf
2025-08-05 Update Edmunds_designs submodule
2025-09-24 pool all np calibration files in one folder
2026-03-25 add npx 2.0 calibration files
2026-03-25 add 3Dneuro holder stl files
